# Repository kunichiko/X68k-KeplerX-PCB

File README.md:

# X68k-KeplerX

## Bus Access Timing

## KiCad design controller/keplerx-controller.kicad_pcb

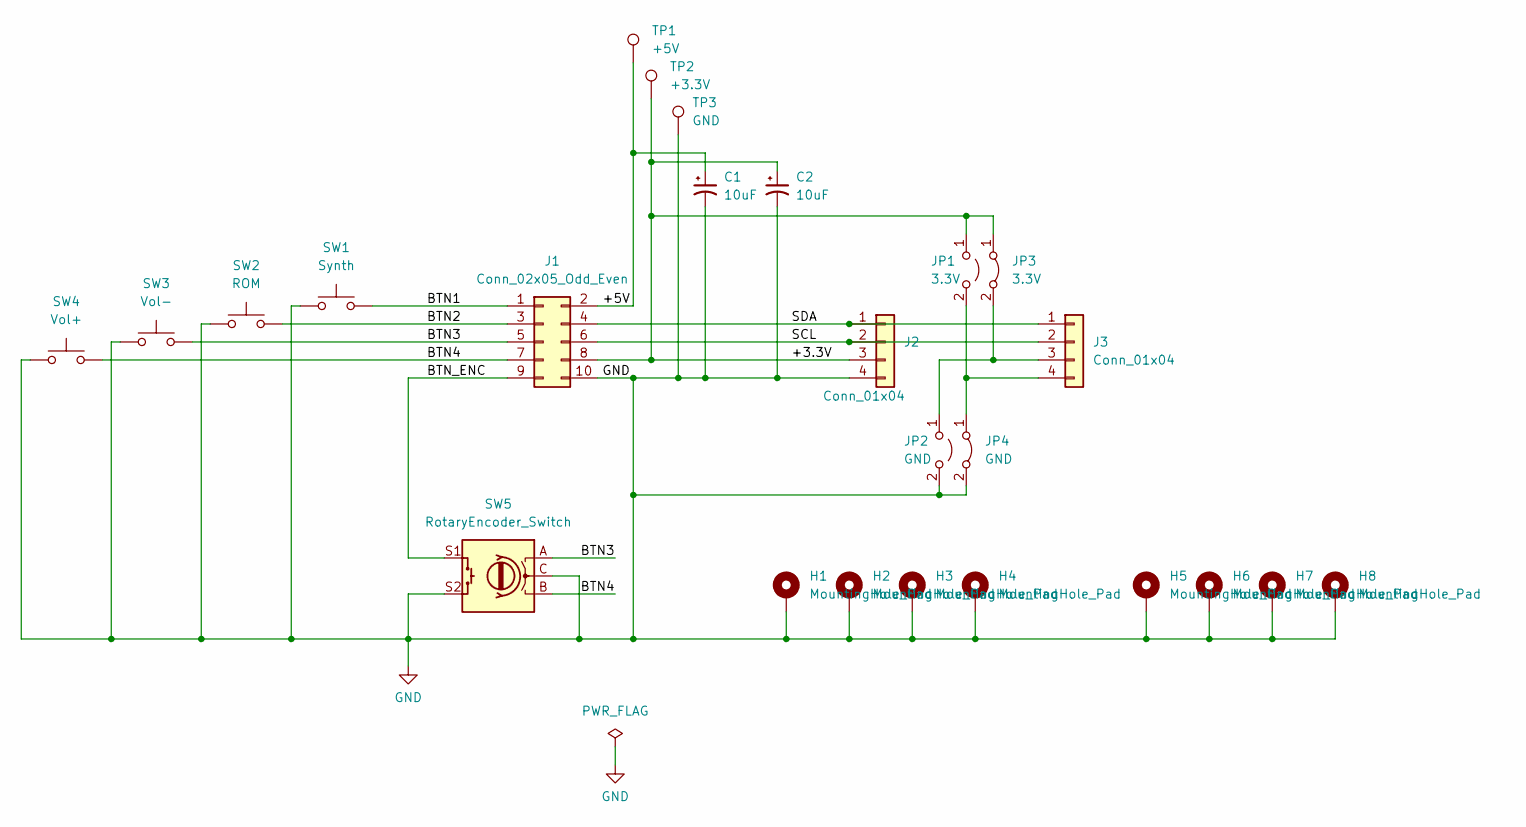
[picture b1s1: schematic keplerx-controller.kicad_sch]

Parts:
C1, C2: 10uF; CP_EIA-3216-10_Kemet-I
H1, H2, H3, H4: MountingHole_Pad; MountingHole_3.2mm_M3_Pad
H5, H6, H7, H8: MountingHole_Pad; MountingHole_2.2mm_M2_ISO7380_Pad
J1: Conn_02x05_Odd_Even; IDC-Header_2x05_P2.54mm_Latch_Horizontal
J2, J3: Conn_01x04; PinSocket_1x04_P2.54mm_Vertical
JP1: 3.3V; SolderJumper-2_P1.3mm_Open_RoundedPad1.0x1.5mm
JP2: GND; SolderJumper-2_P1.3mm_Open_RoundedPad1.0x1.5mm
JP3: 3.3V; SolderJumper-2_P1.3mm_Bridged2Bar_RoundedPad1.0x1.5mm
JP4: GND; SolderJumper-2_P1.3mm_Bridged2Bar_RoundedPad1.0x1.5mm
SW1: Synth; SW_PUSH_6mm
SW2: ROM; SW_PUSH_6mm
SW3: Vol-; SW_PUSH_6mm
SW4: Vol+; SW_PUSH_6mm
SW5: RotaryEncoder_Switch; RotaryEncoder_Alps_EC12E-Switch_Vertical_H20mm
TP1: +5V; TestPoint_THTPad_2.0x2.0mm_Drill1.0mm
TP2: +3.3V; TestPoint_THTPad_2.0x2.0mm_Drill1.0mm
TP3: GND; TestPoint_THTPad_2.0x2.0mm_Drill1.0mm

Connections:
/+3.3V: C2.1, J1.8, J2.3, JP1.1 (A), JP3.1 (A), TP2.1; also elsewhere on the board
/+5V: C1.1, J1.2, TP1.1
/BTN1: J1.1, SW1.2
/BTN2: J1.3, SW2.2
/BTN3: J1.5, SW3.2, SW5.A
/BTN4: J1.7, SW4.2, SW5.B
/BTN_ENC: J1.9, SW5.S1
/SCL: J1.6, J2.2, J3.2
/SDA: J1.4, J2.1, J3.1
GND: C1.2, C2.2, H1.1, H2.1, H3.1, H4.1, H5.1, H6.1, H7.1, H8.1, J1.10, J2.4, JP2.2 (B), JP4.2 (B), SW1.1, SW2.1, SW3.1, SW4.1, SW5.C, SW5.S2, TP3.1; also elsewhere on the board
unnamed 10: J3.3, JP2.1 (A), JP3.2 (B); also elsewhere on the board
unnamed 11: J3.4, JP1.2 (B), JP4.1 (A); also elsewhere on the board

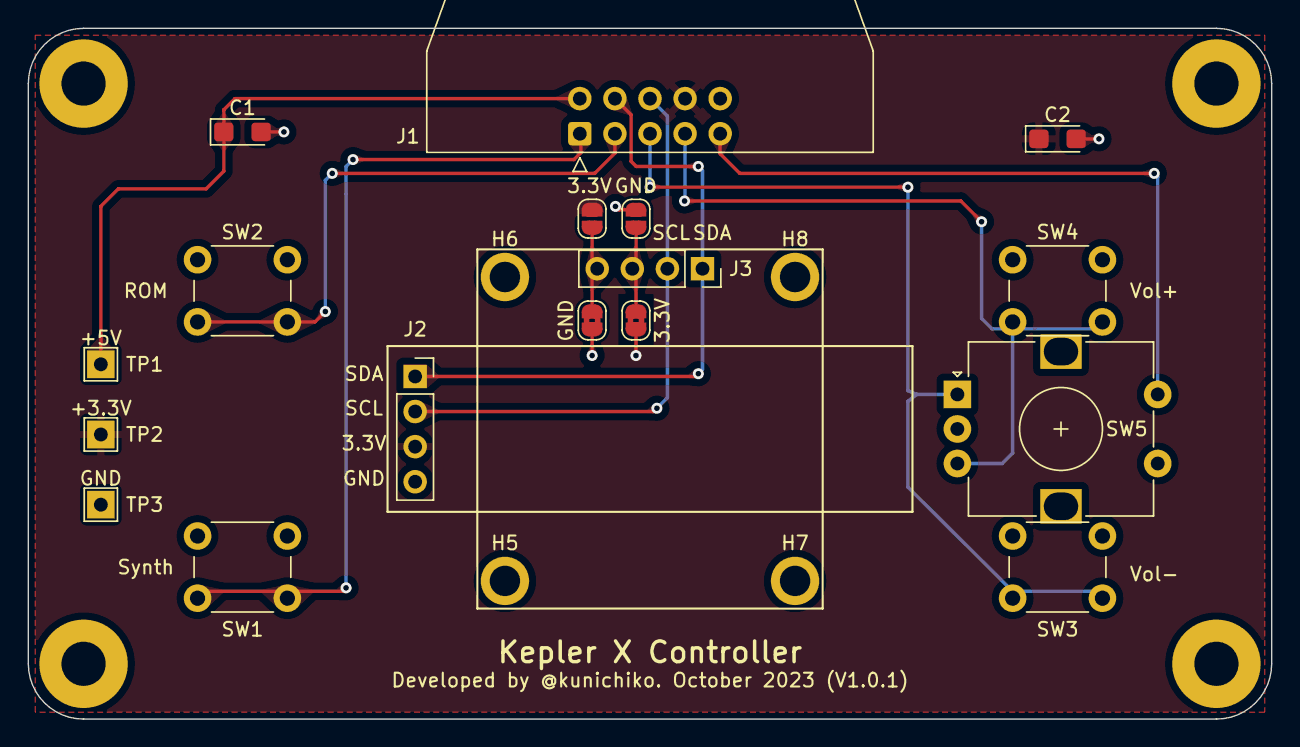
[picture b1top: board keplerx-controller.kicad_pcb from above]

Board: 2 copper layers, 90.0 x 50.0 mm, 25 parts (0 on the bottom side), 12 nets.

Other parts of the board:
3.3V: 3.3V; SolderJumper-2_P1.3mm_Bridged2Bar_RoundedPad1.0x1.5mm
GND: GND; SolderJumper-2_P1.3mm_Bridged2Bar_RoundedPad1.0x1.5mm

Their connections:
/+3.3V: 3.3V.1 (A); also elsewhere on the board
GND: GND.2 (B); also elsewhere on the board
unnamed 10: 3.3V.2 (B); also elsewhere on the board
unnamed 11: GND.1 (A); also elsewhere on the board

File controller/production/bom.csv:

Designator,Footprint,Quantity,Value,LCSC Part #
"C1, C2",CP_Elec_6.3x5.4,2,10uF,
"H1, H2, H3, H4",MountingHole_3.2mm_M3_Pad,4,MountingHole_Pad,
J1,IDC-Header_2x05_P2.54mm_Latch_Horizontal,1,Conn_02x05_Odd_Even,
"J2, J3",PinSocket_1x04_P2.54mm_Vertical,2,Conn_01x04,
"JP1, JP3",SolderJumper-2_P1.3mm_Open_RoundedPad1.0x1.5mm,2,3.3V,
"JP2, JP4",SolderJumper-2_P1.3mm_Open_RoundedPad1.0x1.5mm,2,GND,
SW1,SW_PUSH_6mm,1,Synth,
SW2,SW_PUSH_6mm,1,ROM,
SW3,SW_PUSH_6mm,1,Vol-,
SW4,SW_PUSH_6mm,1,Vol+,
SW5,RotaryEncoder_Alps_EC12E-Switch_Vertical_H20mm,1,RotaryEncoder_Switch,
TP1,TestPoint_THTPad_2.0x2.0mm_Drill1.0mm,1,+5V,
TP2,TestPoint_THTPad_2.0x2.0mm_Drill1.0mm,1,+3.3V,
TP3,TestPoint_THTPad_2.0x2.0mm_Drill1.0mm,1,GND,

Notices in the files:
parts and their libraries:
Copyright 2021 Accelerated Designs. All rights reserved.
